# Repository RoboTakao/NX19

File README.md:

# NX19

Summary:  
Japanese http://robotakao.web.fc2.com/NX19/index.html  
English http://robotakao.web.fc2.com/NX19/e/index.html

[Controll with Dabble]  
&emsp;M5Stamp C3 sketch : NX19_M5Stamp_C3_ik_UnitV_IMU.ino  

[Cotroll with JoyC via BLE]  
&emsp;M5Stamp C3 sketch : NX19_M5Stamp_C3_ik_UnitV_IMU_joyC.ino  
&emsp;M5Stamp C3 sketch : NX19_M5Stamp_S3_ik_UnitV_IMU_joyC.ino  
&emsp;M5tickC with JoyC sketch : NX19_JoyC_M5StickC_BLE.ino  

[Unit V]  
&emsp;UnitV Python code : NX19_track_Face.py

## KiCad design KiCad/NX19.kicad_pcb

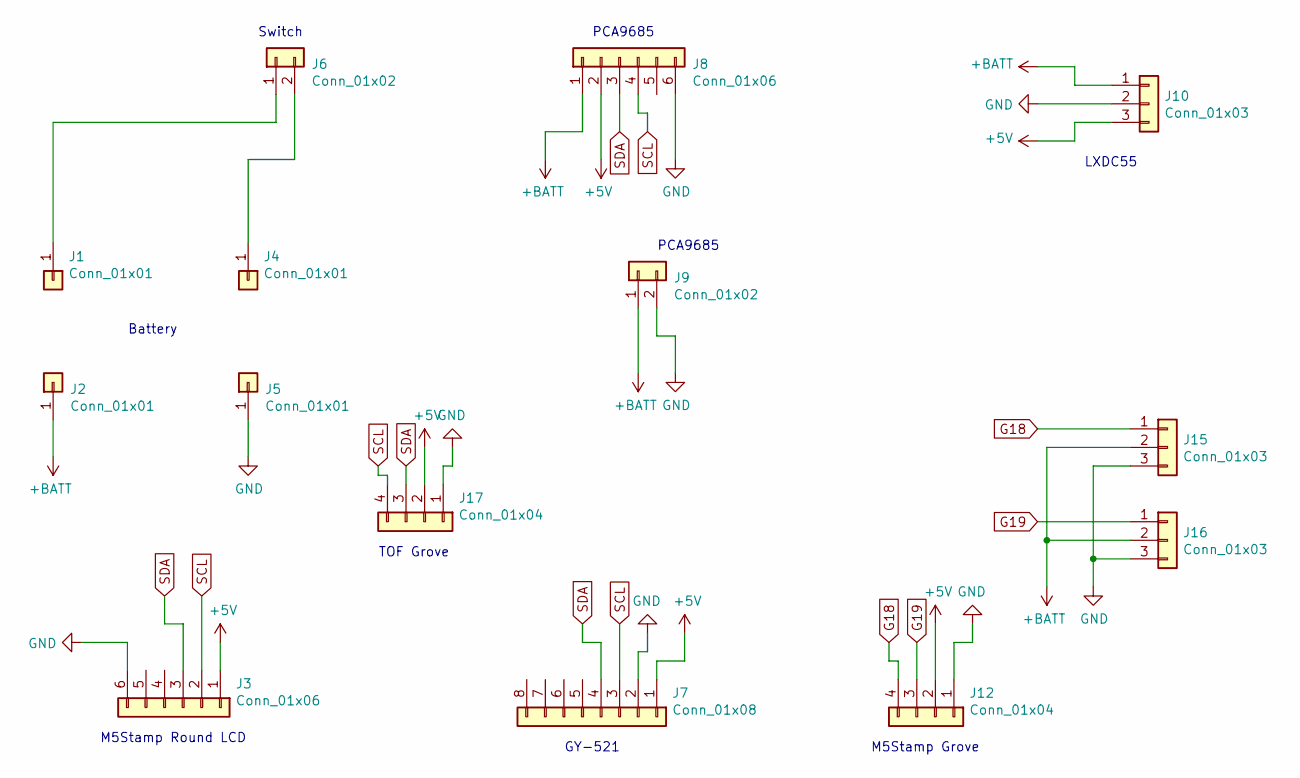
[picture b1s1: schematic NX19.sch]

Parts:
J1, J2, J4, J5: Conn_01x01; PinHeader_1x01_P2.54mm_Vertical
J3, J8: Conn_01x06; PinHeader_1x06_P2.54mm_Vertical
J6: Conn_01x02; JST_XH_B2B-XH-A_1x02_P2.50mm_Vertical
J7: Conn_01x08; PinSocket_1x08_P2.54mm_Vertical
J9: Conn_01x02; PinHeader_1x02_P2.54mm_Vertical
J10, J15, J16: Conn_01x03; PinHeader_1x03_P2.54mm_Vertical
J12, J17: Conn_01x04; PinHeader_1x04_P2.54mm_Vertical

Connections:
+5V: J3.1, J7.1, J8.2, J10.3, J12.2, J17.2
+BATT: J2.1, J8.1, J9.1, J10.1, J15.2, J16.2
G18: J12.4, J15.1
G19: J12.3, J16.1
GND: J3.6, J5.1, J7.2, J8.6, J9.2, J10.2, J12.1, J15.3, J16.3, J17.1
unnamed: J1.1, J6.1
unnamed: J4.1, J6.2
SCL: J3.2, J7.3, J8.4, J17.4
SDA: J3.3, J7.4, J8.3, J17.3

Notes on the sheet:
GY-521
M5Stamp Round LCD
LXDC55
PCA9685
Battery
Switch
M5Stamp Grove
TOF Grove

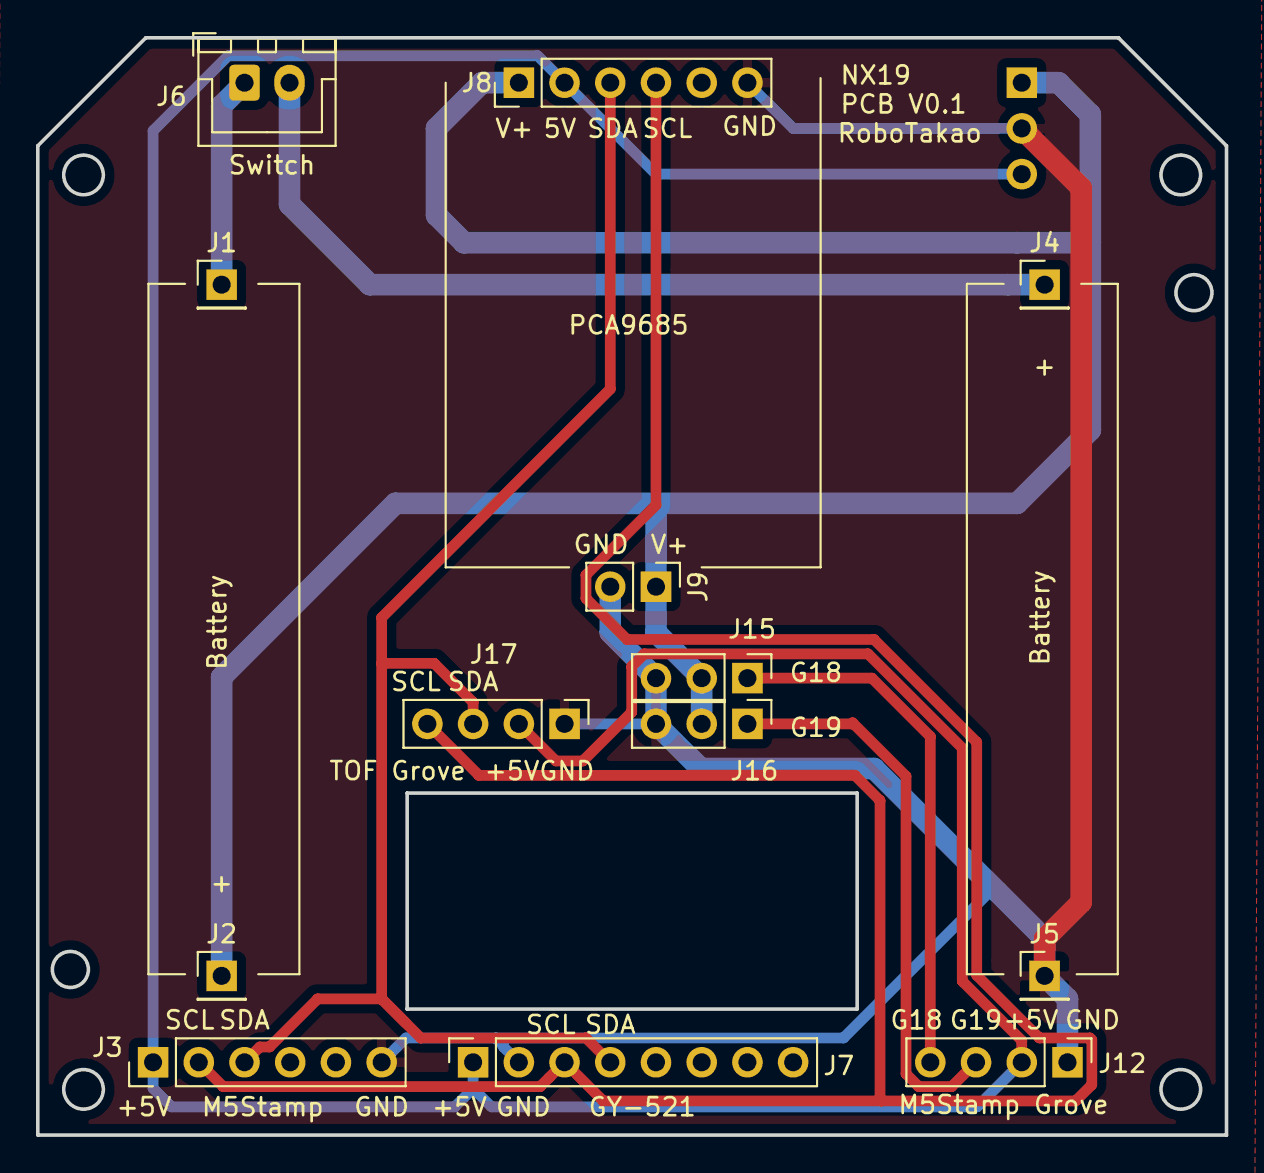
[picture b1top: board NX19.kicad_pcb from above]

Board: 2 copper layers, 66.0 x 61.0 mm, 14 parts (1 on the bottom side), 9 nets.

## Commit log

2023-02-07 README.md を更新
